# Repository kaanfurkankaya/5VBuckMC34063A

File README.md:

# MC34063A ile 5V Düşürücü Regülatör

Bu proje, **MC34063AP** anahtarlamalı regülatör entegresi ile hazırlanmış bir **5V DC buck regülatör** KiCad tasarımıdır. Kart; DC girişten sabit **5V DC çıkış** üretmek için tasarlanmıştır ve through-hole parçalarla kolay montaj hedeflenmiştir.

> Not: Kart üzerindeki eski notlarda giriş 6.5-9V gibi düşünülmüş olabilir. MC34063A datasheet'inde entegre giriş aralığı **3V-40V** olarak verilir ve 5V/500mA düşürücü örneği **15V-25V giriş** ile gösterilir. Bu yüzden tasarım 9V ile sınırlı değildir; ancak üst giriş sınırı kullanılan kondansatör, diyot, bobin ve ısınma koşullarına göre doğrulanmalıdır.

## Görseller

### Şematik

### PCB Görünümü

### 3D Kart Görünümü

## Teknik Özellikler

- **Giriş:** 6.5V DC ve üzeri
- **Çıkış:** 5V DC
- **Hedef akım:** 300mA sürekli, 500mA maksimum
- **Regülatör entegresi:** MC34063AP, DIP-8
- **Topoloji:** Düşürücü / buck converter
- **PCB boyutu:** Yaklaşık 77mm x 30mm
- **Tasarım aracı:** KiCad 9.0

## Devre Notları

Datasheet'e göre MC34063A; yükseltici, düşürücü ve tersleyici regülatör uygulamaları için gerekli osilatör, referans, karşılaştırıcı, akım sınırlama ve anahtarlama transistörünü içinde barındırır.

Bu kartta çıkış gerilimi geri besleme dirençleriyle ayarlanır:

```text
Vout = 1.25V x (1 + R3 / R1)
R1 = 1k
R3 = 3k
Vout ~= 5V
```

Akım sınırlama direnci `R2 = 0.33R` seçilmiştir. Datasheet formülüne göre yaklaşık tepe anahtar akımı:

```text
Ipk ~= 0.3V / Rsc
Ipk ~= 0.3V / 0.33R ~= 0.9A
```

Bu değer çıkış akımıyla aynı şey değildir; bobin doyma akımı, diyot akımı, kart ısısı ve giriş gerilimi mutlaka dikkate alınmalıdır.

## Ana Parçalar

| Referans | Değer / Parça | Açıklama |
|---|---:|---|
| U1 | MC34063AP | Anahtarlamalı regülatör entegresi |
| D1 | 1N5819 | Schottky diyot |
| L1 | 220uH | Buck bobini |
| R1 | 1k | Geri besleme alt direnci |
| R3 | 3k | Geri besleme üst direnci |
| R2 | 0.33R | Akım sınırlama direnci |
| C1 | 470pF | Zamanlama kondansatörü |
| C2 | 100uF | Giriş kondansatörü |
| C3 | 470uF | Çıkış kondansatörü |
| C4 | 100nF | Bypass kondansatörü |
| J1 | DC Input | Giriş klemensi |
| J2 | DC Output | 5V çıkış klemensi |

## Dosyalar

- `5VBuckMC34063A.kicad_sch`: Devre şeması
- `5VBuckMC34063A.kicad_pcb`: PCB yerleşimi
- `5VBuckMC34063A.kicad_pro`: KiCad proje dosyası
- `5VBuckMC34063A-ÖnYüz.pdf`: Ön yüz baskı çıktısı
- `5VBuckMC34063A-Bakır.pdf`: Bakır yüz baskı çıktısı
- `5VBuckMC34063A-backups/`: KiCad otomatik yedekleri

## Kullanım

1. `J1` klemensinden DC giriş uygulayın.
2. Polariteye dikkat edin: `VIN+` ve `GND` ters bağlanmamalıdır.
3. `J2` klemensinden 5V çıkış alın.
4. İlk testte akım sınırlı güç kaynağı kullanın.
5. 9V üzeri girişlerde parça voltaj değerlerini ve regülatör sıcaklığını kontrol edin.

## Datasheet

- [TI MC34063A / MC33063A Datasheet]([https://www.onsemi.com/download/data-sheet/pdf/mc34063a-d.pdf](https://www.ti.com/lit/ds/symlink/mc34063a.pdf))

## Uyarı

Bu kart hobi ve prototip amaçlı bir tasarımdır. Yüksek giriş gerilimlerinde, yüksek yük akımlarında veya uzun süreli çalışmada sıcaklık, ripple ve parça limitleri ölçülerek doğrulanmalıdır.

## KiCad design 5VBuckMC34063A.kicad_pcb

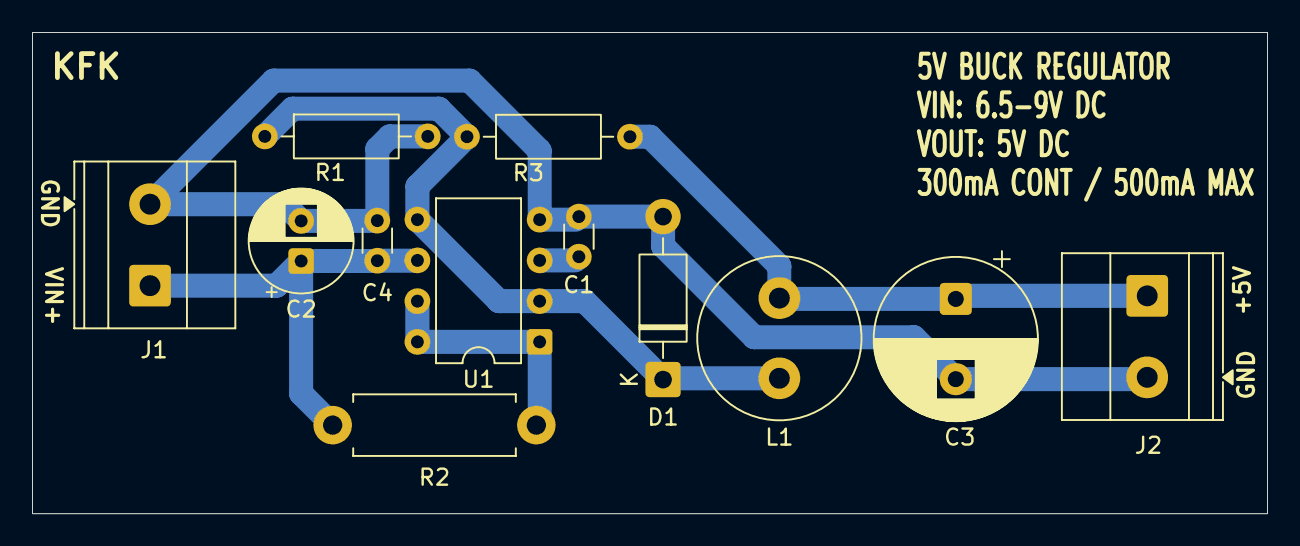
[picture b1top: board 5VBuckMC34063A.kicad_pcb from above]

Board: 2 copper layers, 77.0 x 30.0 mm, 12 parts (0 on the bottom side), 6 nets.

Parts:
C1: 470pF; C_Disc_D3.0mm_W1.6mm_P2.50mm
C2: 100uF; CP_Radial_D6.3mm_P2.50mm
C3: 470uF; CP_Radial_D10.0mm_P5.00mm
C4: 100nF; C_Disc_D3.0mm_W1.6mm_P2.50mm
D1: 1N5819; D_DO-41_SOD81_P10.16mm_Horizontal
J1: DC Input; TerminalBlock_Phoenix_MKDS-1,5-2-5.08_1x02_P5.08mm_Horizont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
J2: 5V DC Output; TerminalBlock_Phoenix_MKDS-1,5-2-5.08_1x02_P5.08mm_Horizont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
L1: 220uH; L_Radial_D10.0mm_P5.00mm_Fastron_07M
R1: 1k; R_Axial_DIN0207_L6.3mm_D2.5mm_P10.16mm_Horizontal
R2: 0.33R; R_Axial_DIN0411_L9.9mm_D3.6mm_P12.70mm_Horizontal
R3: 3k; R_Axial_DIN0207_L6.3mm_D2.5mm_P10.16mm_Horizontal
U1: MC34063AP; DIP-8_W7.62mm

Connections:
GND: C1.2, C2.2, C3.2, C4.2, D1.2 (A), J1.1, J2.1, R1.2, U1.4 (GND)
unnamed: D1.1 (K), L1.1, R1.1, R3.1, U1.2 (SwE), U1.5 (Vfb)
unnamed: C2.1, C4.1, J1.2, R2.2, U1.6 (Vin)
unnamed: C3.1, J2.2, L1.2, R3.2
unnamed: R2.1, U1.1 (SwC), U1.7 (Ipk), U1.8 (DC)
unnamed: C1.1, U1.3 (TC)

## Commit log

2026-05-22 README ekle
2026-05-22 Update datasheet link for MC34063A / MC33063A
2026-05-22 README gorsellerini ekle
2026-05-22 Update input voltage specification in README
    Removed the note about the input voltage limit.
